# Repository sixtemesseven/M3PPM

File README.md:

# M3PPM
 Modular 3 phase power meter, based on D!-Mini (ESP8266) and the ATM90E32AS meter chip.

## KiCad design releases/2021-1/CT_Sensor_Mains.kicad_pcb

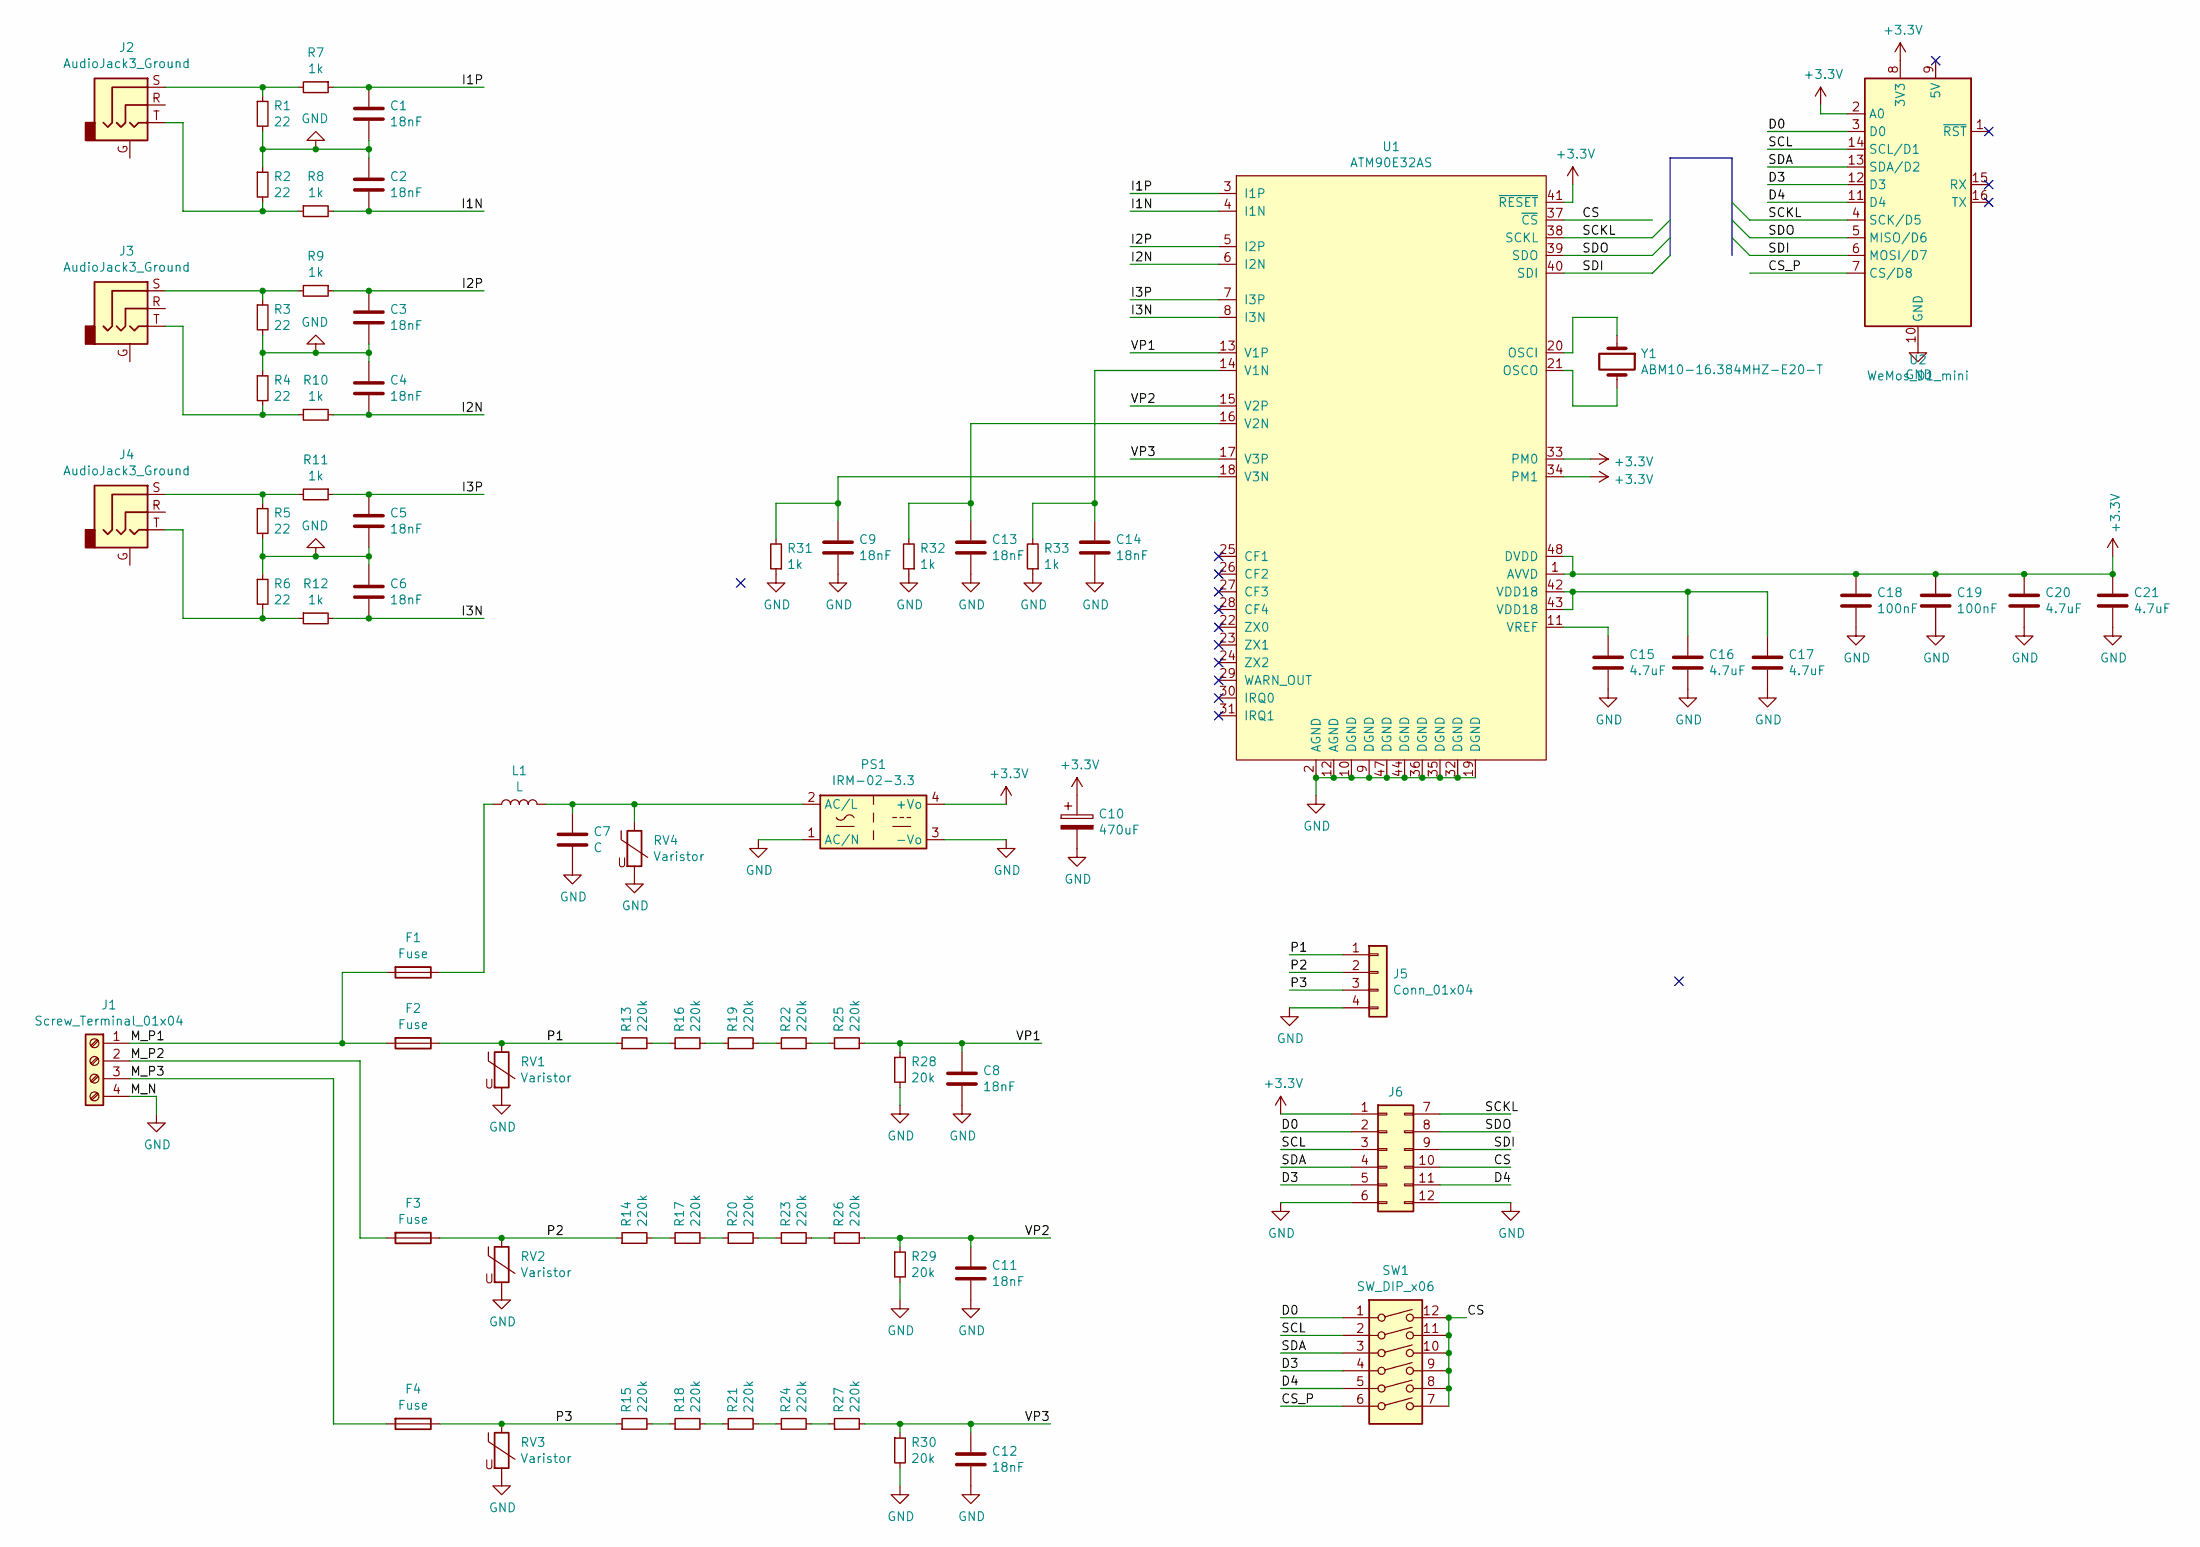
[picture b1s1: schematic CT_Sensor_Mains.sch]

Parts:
C1, C2, C3, C4, C5, C6, C8, C9, C11, C12, C13, C14: 18nF; C_0603_1608Metric
C7: C; C_Rect_L13.5mm_W4.0mm_P10.00mm_FKS3_FKP3_MKS4
C10: 470uF; CP_Radial_D10.0mm_P5.00mm
C15, C16, C17, C20, C21: 4.7uF; C_0805_2012Metric
C18, C19: 100nF; C_0603_1608Metric
F1, F2, F3, F4: Fuse; Fuse_1206_3216Metric_Pad1.42x1.75mm_HandSolder
J1: Screw_Terminal_01x04; TerminalBlock_Phoenix_MKDS-1,5-4_1x04_P5.00mm_Horizontal
J2, J3, J4: AudioJack3_Ground; Jack_3.5mm_CUI_SJ-3523-SMT_Horizontal
J5: Conn_01x04; PinHeader_1x04_P2.54mm_Vertical
J6: Conn_02x06_Top_Bottom; PinHeader_2x06_P2.54mm_Vertical
L1: L; L_Radial_D12.0mm_P5.00mm_Fastron_11P
PS1: IRM-02-3.3; Converter_ACDC_MeanWell_IRM-02-xx_THT
R1, R2, R3, R4, R5, R6: 22; R_0805_2012Metric_Pad1.20x1.40mm_HandSolder
R7, R8, R9, R10, R11, R12, R31, R32, R33: 1k; R_0805_2012Metric_Pad1.20x1.40mm_HandSolder
R13, R14, R15, R16, R17, R18, R19, R20, R21, R22, R23, R24, R25, R26, R27: 220k; R_0805_2012Metric_Pad1.20x1.40mm_HandSolder
R28, R29, R30: 20k; R_0805_2012Metric_Pad1.20x1.40mm_HandSolder
RV1, RV2, RV3, RV4: Varistor; RV_Disc_D7mm_W4mm_P5mm
SW1: SW_DIP_x06; SW_DIP_SPSTx06_Slide_9.78x17.42mm_W7.62mm_P2.54mm
U1: ATM90E32AS; TQFP-48_7x7mm_P0.5mm
U2: WeMos_D1_mini; WEMOS_D1_mini_light
Y1: ABM10-16.384MHZ-E20-T‎; Crystal_SMD_Abracon_ABM10-4Pin_2.5x2.0mm

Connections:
+3V3: C10.1, C18.1, C19.1, C20.1, C21.1, J6.1, PS1.4 (+Vo), U1.1 (AVVD), U1.33 (PM0), U1.34 (PM1), U1.41 (~RESET), U1.48 (DVDD), U2.2 (A0), U2.8 (3V3)
/CS: J6.10, SW1.7, SW1.8, SW1.9, SW1.10, SW1.11, SW1.12, U1.37 (~CS)
/CS_P: SW1.6, U2.7 (CS/D8)
/D0: J6.2, SW1.1, U2.3 (D0)
/D3: J6.5, SW1.4, U2.12 (D3)
/D4: J6.11, SW1.5, U2.11 (D4)
/I1N: C2.1, R8.2, U1.4 (I1N)
/I1P: C1.2, R7.1, U1.3 (I1P)
/I2N: C4.1, R10.2, U1.6 (I2N)
/I2P: C3.2, R9.1, U1.5 (I2P)
/I3N: C6.1, R12.2, U1.8 (I3N)
/I3P: C5.2, R11.1, U1.7 (I3P)
/M_P1: F1.2, F2.2, J1.1
/M_P2: F3.2, J1.2
/M_P3: F4.2, J1.3
/P1: F2.1, J5.1, R13.1, RV1.1
/P2: F3.1, J5.2, R14.1, RV2.1
/P3: F4.1, J5.3, R15.1, RV3.1
/SCKL: J6.7, U1.38 (SCKL), U2.4 (SCK/D5)
/SCL: J6.3, SW1.2, U2.14 (SCL/D1)
/SDA: J6.4, SW1.3, U2.13 (SDA/D2)
/SDI: J6.9, U1.40 (SDI), U2.6 (MOSI/D7)
/SDO: J6.8, U1.39 (SDO), U2.5 (MISO/D6)
/VP1: C8.2, R25.2, R28.1, U1.13 (V1P)
/VP2: C11.2, R26.2, R29.1, U1.15 (V2P)
/VP3: C12.2, R27.2, R30.1, U1.17 (V3P)
GND: C1.1, C2.2, C3.1, C4.2, C5.1, C6.2, C7.2, C8.1, C9.1, C10.2, C11.1, C12.1, C13.1, C14.1, C15.2, C16.2, C17.2, C18.2, C19.2, C20.2, C21.2, J1.4, J5.4, J6.6, J6.12, PS1.1 (AC/N), PS1.3 (-Vo), R1.2, R2.1, R3.2, R4.1, R5.2, R6.1, R28.2, R29.2, R30.2, R31.1, R32.1, R33.1, RV1.2, RV2.2, RV3.2, RV4.2, U1.2 (AGND), U1.9 (DGND), U1.10 (DGND), U1.12 (AGND), U1.19 (DGND), U1.32 (DGND), U1.35 (DGND), U1.36 (DGND), U1.44 (DGND), U1.47 (DGND), U2.10 (GND)
unnamed: C7.1, L1.2, PS1.2 (AC/L), RV4.1
unnamed: C9.2, R31.2, U1.18 (V3N)
unnamed: C13.2, R32.2, U1.16 (V2N)
unnamed: C14.2, R33.2, U1.14 (V1N)
unnamed: C15.1, U1.11 (VREF)
unnamed: C16.1, C17.1, U1.42 (VDD18), U1.43 (VDD18)
unnamed: F1.1, L1.1
unnamed: J2.S, R1.1, R7.2
unnamed: J2.T, R2.2, R8.1
unnamed: J3.S, R3.1, R9.2
unnamed: J3.T, R4.2, R10.1
unnamed: J4.S, R5.1, R11.2
unnamed: J4.T, R6.2, R12.1
unnamed: R13.2, R16.1
unnamed: R14.2, R17.1
unnamed: R15.2, R18.1
unnamed: R16.2, R19.1
unnamed: R17.2, R20.1
unnamed: R18.2, R21.1
unnamed: R19.2, R22.1
unnamed: R20.2, R23.1
unnamed: R21.2, R24.1
unnamed: R22.2, R25.1
unnamed: R23.2, R26.1
unnamed: R24.2, R27.1
unnamed: U1.20 (OSCI), Y1.1
unnamed: U1.21 (OSCO), Y1.2

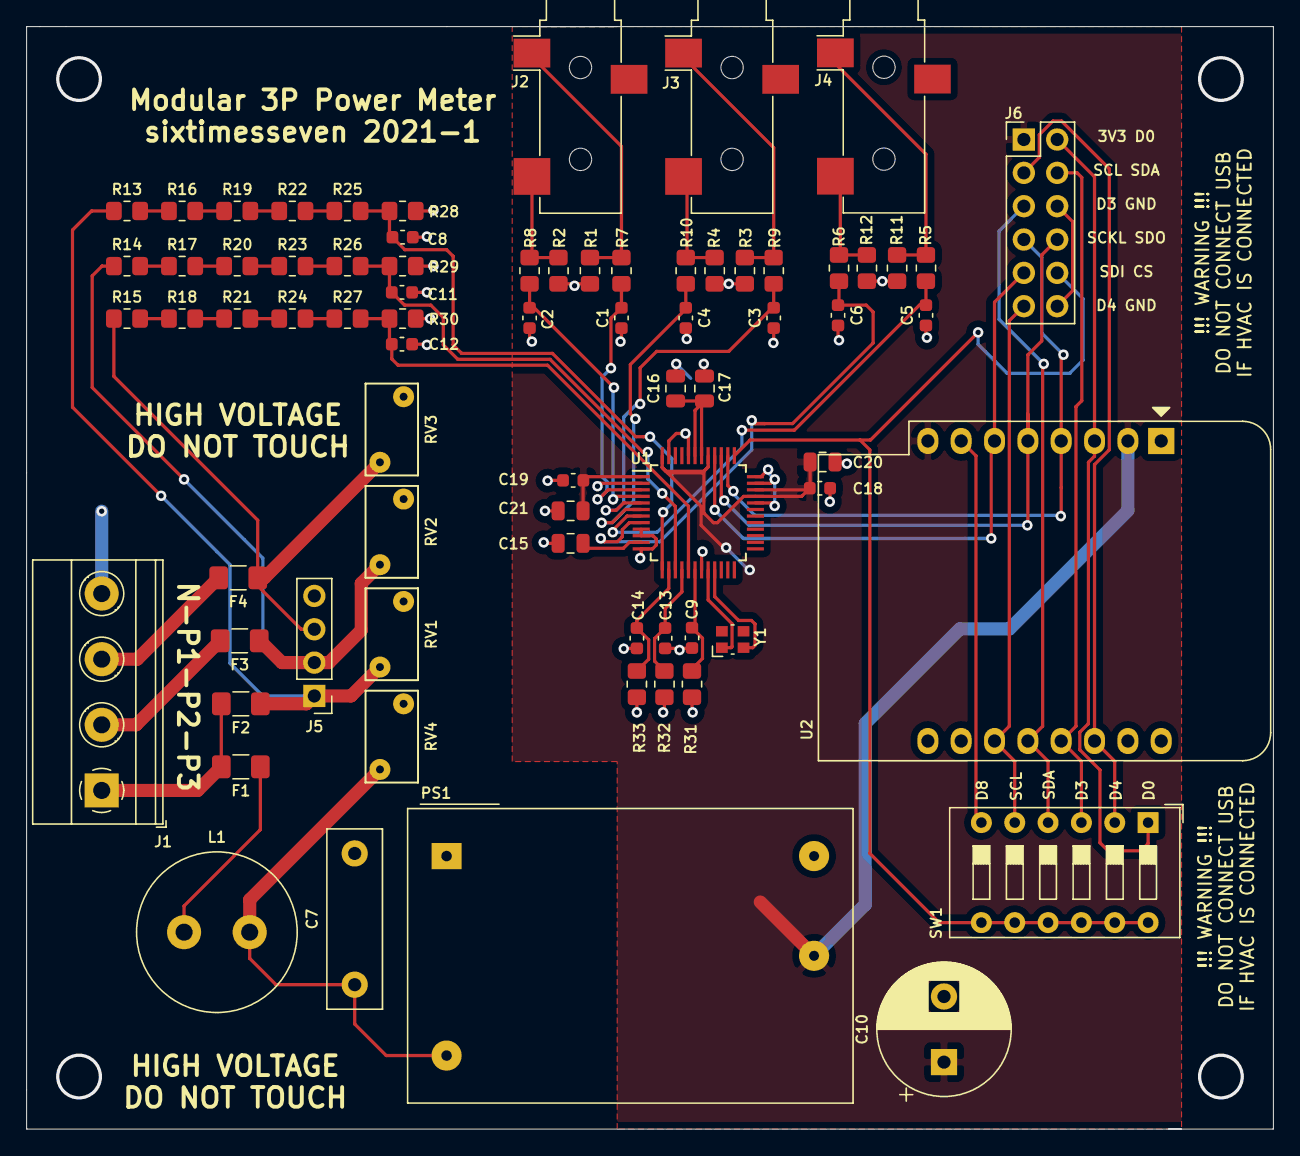
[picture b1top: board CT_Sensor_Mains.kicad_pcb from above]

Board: 2 copper layers, 95.0 x 84.0 mm, 74 parts (0 on the bottom side), 54 nets.

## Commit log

2021-08-26 Initial
    Initial hardware project. untested.
2021-08-26 render
